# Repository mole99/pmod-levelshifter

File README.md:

# pmod-levelshifter
A bidirectional levelshifter designed in KiCad to control higher voltages on an FPGA.

Access the interactive BOM [here](https://htmlpreview.github.io/?https://github.com/mole99/pmod-levelshifter/blob/main/ibom/ibom.html).

I designed this board to interface a keyboard over a PS/2 port. The logic level of the keyboard is 5V whereas the FPGAs IOs run at 3.3V. The `pmod-levelshifter` relays a signal from the HV side to the LV side and vice versa. When no side is driven, the lines are pulled high. 8 IOs are supported.

# Screenshots

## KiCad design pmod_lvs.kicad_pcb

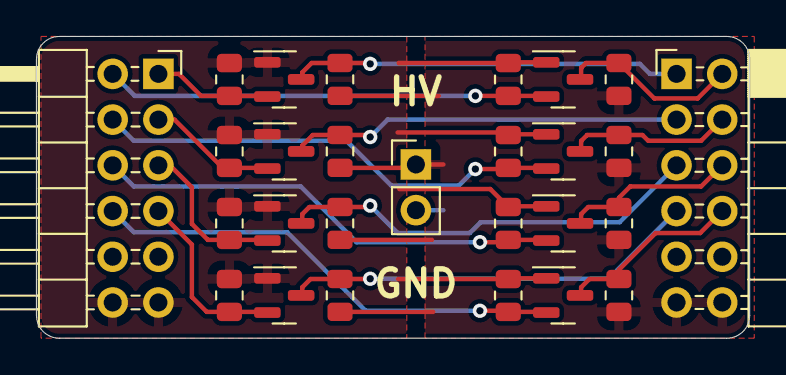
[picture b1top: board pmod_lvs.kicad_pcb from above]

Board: 2 copper layers, 39.6 x 16.8 mm, 27 parts (0 on the bottom side), 19 nets.

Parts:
J1: PMOD_Socket; PMODSocket_2x06_P2.54mm_Horizontal
J2: PMOD_Header; PMODHeader_2x06_P2.54mm_Horizontal
J3: HV_connector; PinHeader_1x02_P2.54mm_Vertical
Q1, Q2, Q3, Q4, Q5, Q6, Q7, Q8: BSS138; SOT-23
R1, R2, R3, R4, R5, R6, R7, R8, R9, R10, R11, R12, R13, R14, R15, R16: 10k; R_0805_2012Metric

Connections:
+3V3: J2.6, J2.12, Q1.1 (G), Q2.1 (G), Q3.1 (G), Q4.1 (G), Q5.1 (G), Q6.1 (G), Q7.1 (G), Q8.1 (G), R1.1, R3.1, R5.1, R7.1, R9.1, R11.1, R13.1, R15.1
+5V: J1.6, J1.12, J3.1, R2.1, R4.1, R6.1, R8.1, R10.1, R12.1, R14.1, R16.1
GND: J1.5, J1.11, J2.5, J2.11, J3.2
HV0: J1.1, Q1.3 (D), R2.2
HV1: J1.2, Q2.3 (D), R4.2
HV2: J1.3, Q3.3 (D), R6.2
HV3: J1.4, Q4.3 (D), R8.2
HV4: J1.7, Q5.3 (D), R10.2
HV5: J1.8, Q6.3 (D), R12.2
HV6: J1.9, Q7.3 (D), R14.2
HV7: J1.10, Q8.3 (D), R16.2
LV0: J2.1, Q1.2 (S), R1.2
LV1: J2.2, Q2.2 (S), R3.2
LV2: J2.3, Q3.2 (S), R5.2
LV3: J2.4, Q4.2 (S), R7.2
LV4: J2.7, Q5.2 (S), R9.2
LV5: J2.8, Q6.2 (S), R11.2
LV6: J2.9, Q7.2 (S), R13.2
LV7: J2.10, Q8.2 (S), R15.2

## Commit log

2021-12-30 Populate project
2022-01-02 Migrate to KiCad 6
2022-01-02 Update images
2022-01-02 Add IBOM
2022-01-02 Add a link to the IBOM
